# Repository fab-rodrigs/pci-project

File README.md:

# pci-project

[Documento Relatório](https://docs.google.com/document/d/15hXtcBPBoGtcoUK8AWU8GS6HNx2_iXNRZ9IdS8J2mAE/edit?usp=sharing)

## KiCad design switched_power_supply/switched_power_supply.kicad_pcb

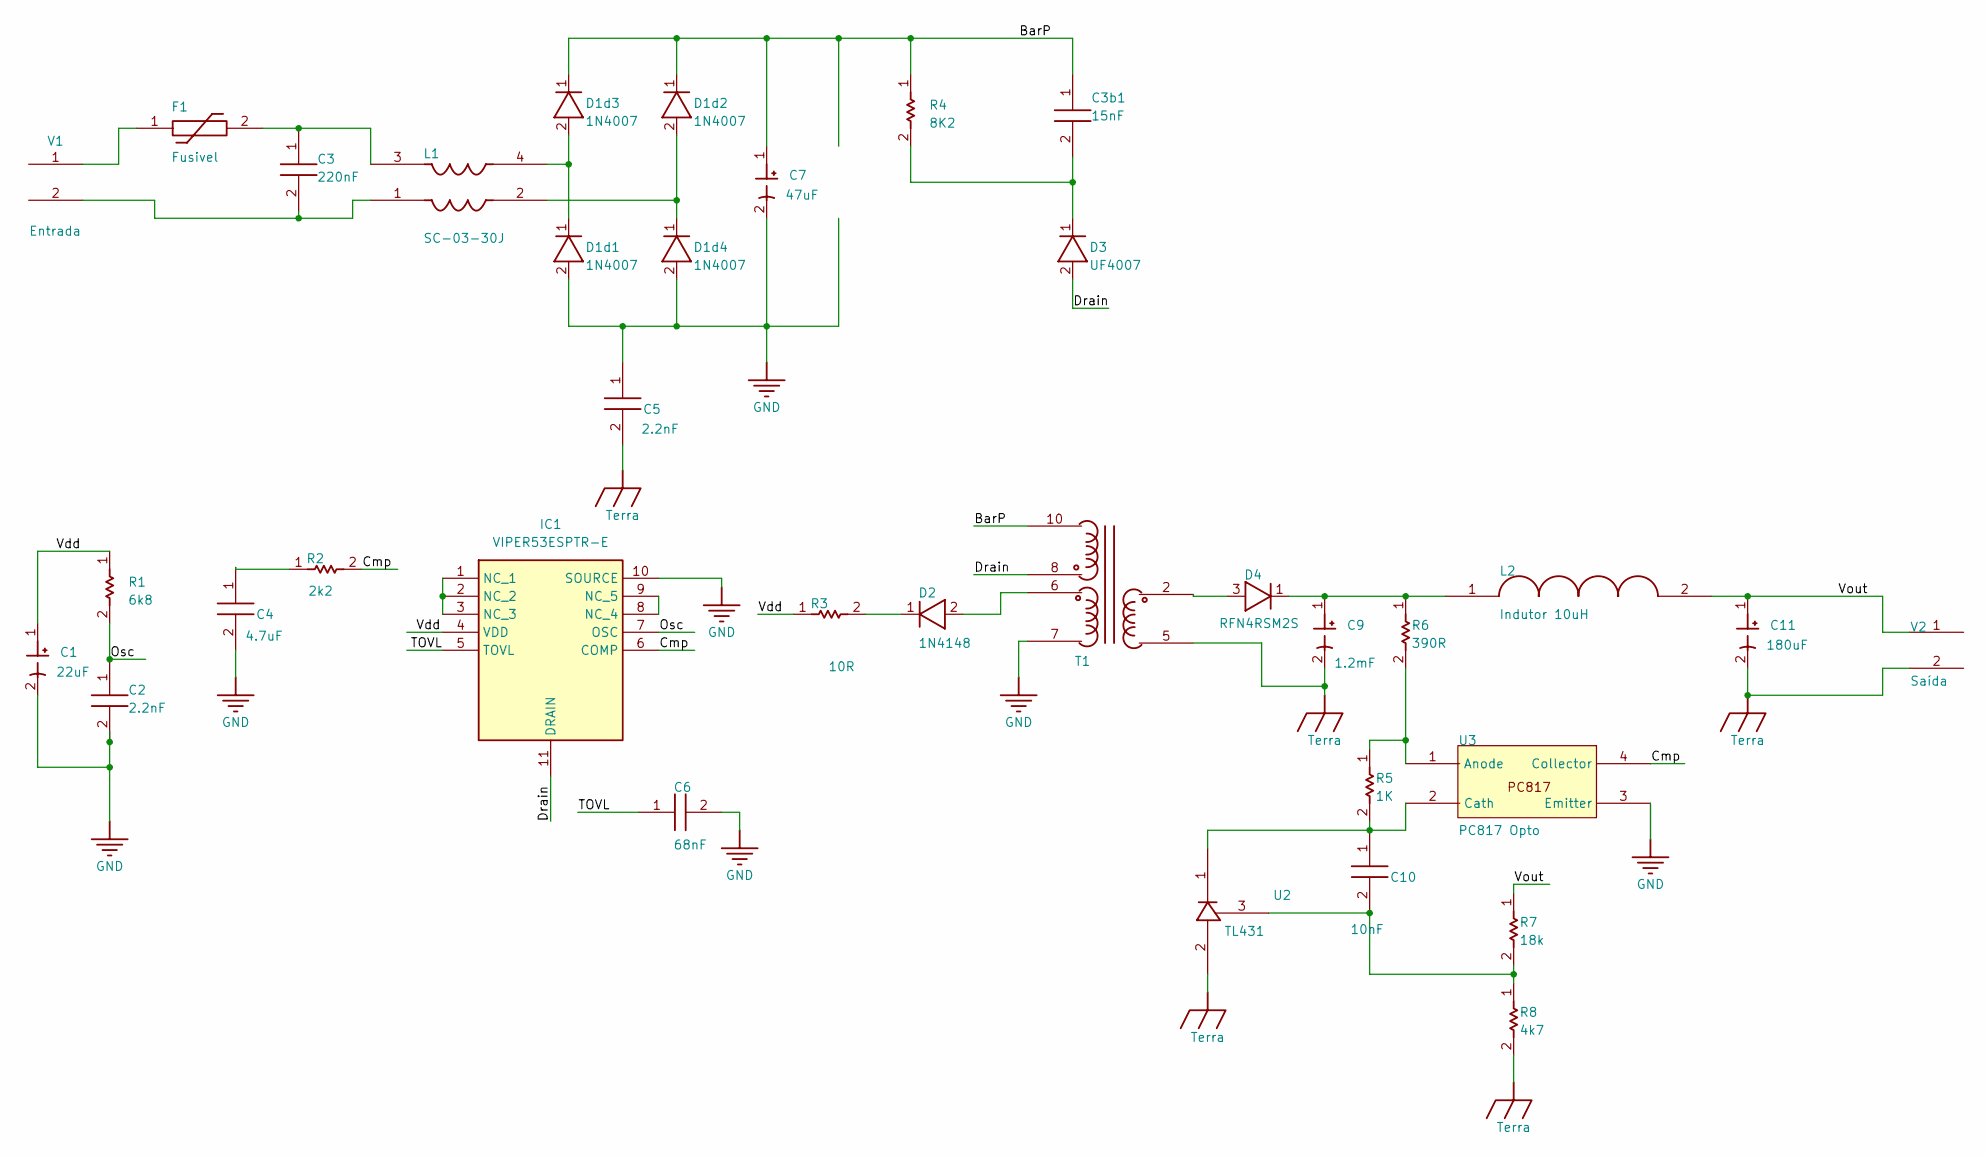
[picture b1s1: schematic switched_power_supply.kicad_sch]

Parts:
C1: Capacitor_Eletrolitico; EEHZT1E331UP
C2: Capacitor Ceramico; CAPC1608X97N
C3: Capacitor_Filme; C_Rect_L18.0mm_W5.0mm_P15.00mm_FKS3_FKP3
C3b1: Capacitor_Filme; C_Rect_L18.0mm_W6.0mm_P15.00mm_FKS3_FKP3; VOLTAGE 15nF
C4: Capacitor Ceramico; CAPC3225X94N
C5: Capacitor_Filme; C_Rect_L7.0mm_W2.5mm_P5.00mm
C6: Capacitor_Filme; CAPC3216X170N
C7: Capacitor_Eletrolitico; CP_Radial_D16.0mm_P7.50mm
C9: Capacitor_Eletrolitico; EEEFK0J332AV
C10: Capacitor_Filme; C1206
C11: Capacitor_Eletrolitico; 16SVPG330M
D1d1, D1d2, D1d3, D1d4: 1N4007; D_A-405_P12.70mm_Horizontal
D2: 1N4148; D_DO-35_SOD27_P7.62mm_Horizontal
D3: UF4007; D_DO-41_SOD81_P7.62mm_Horizontal
D4: RFN4RSM2S; TO-277A
F1: Fusivel; Fuse_Bourns_MF-RG600
IC1: VIPER53ESPTR-E; SOIC127P1410X370-11N; Mouser Part Number 511-VIPER53ESPTR-E
L1: SC-03-30J; L_Axial_L20.0mm_D8.0mm_P25.40mm_Horizontal
L2: Indutor 10uH; INDPM108102X400N
R1, R2, R3, R5: Resistor SMD; R_0805_2012Metric; ML_PART *
R4: Resistor PTH; R_Axial_Power_L25.0mm_W6.4mm_P30.48mm; ML_PART *
R6, R7, R8: Resistor PTH; R_0805_2012Metric; ML_PART *
T1: Transformador_1x2; TRZ 25.010.2
U2: TL431; SOT95P237X112-3N
U3: PC817 Opto; SOIC254P960X420-4N
V1: Entrada; TerminalBlock_bornier-2_P5.08mm
V2: Saída; TerminalBlock_bornier-2_P5.08mm

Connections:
/BarP: C3b1.1, C7.1, D1d2.1 (K), D1d3.1 (K), R4.1, T1.10
/Cmp: IC1.6 (COMP), R2.2, U3.4 (Collector)
/Drain: D3.2 (A), IC1.11 (DRAIN), T1.8
/Osc: C2.1, IC1.7 (OSC), R1.2
/TOVL: C6.1, IC1.5 (TOVL)
/Vdd: C1.1, IC1.4 (VDD), R1.1, R3.1
/Vout: C11.1, L2.2, R7.1, V2.1
GND: C1.2, C2.2, C4.2, C5.1, C6.2, C7.2, D1d1.2 (A), D1d4.2 (A), IC1.10 (SOURCE), T1.7, U3.3 (Emitter)
unnamed: C3.1, F1.2, L1.3
unnamed: C3.2, L1.1, V1.2
unnamed: C4.1, R2.1
unnamed: C10.2, R7.2, R8.1, U2.3
unnamed: D1d1.1 (K), D1d3.2 (A), L1.4
unnamed: D1d2.2 (A), D1d4.1 (K), L1.2
unnamed: D2.2 (A), T1.6
unnamed: D2.1 (K), R3.2
unnamed: C3b1.2, D3.1 (K), R4.2
unnamed: D4.3 (A), T1.2
unnamed: C9.1, D4.1 (K), L2.1, R6.1
unnamed: F1.1, V1.1
unnamed: IC1.1 (NC_1), IC1.2 (NC_2), IC1.3 (NC_3)
unnamed: IC1.8 (NC_4), IC1.9 (NC_5)
unnamed: R5.1, R6.2, U3.1 (Anode)
unnamed: C10.1, R5.2, U2.1, U3.2 (Cath)
Terra: C5.2, C9.2, C11.2, R8.2, T1.5, U2.2, V2.2

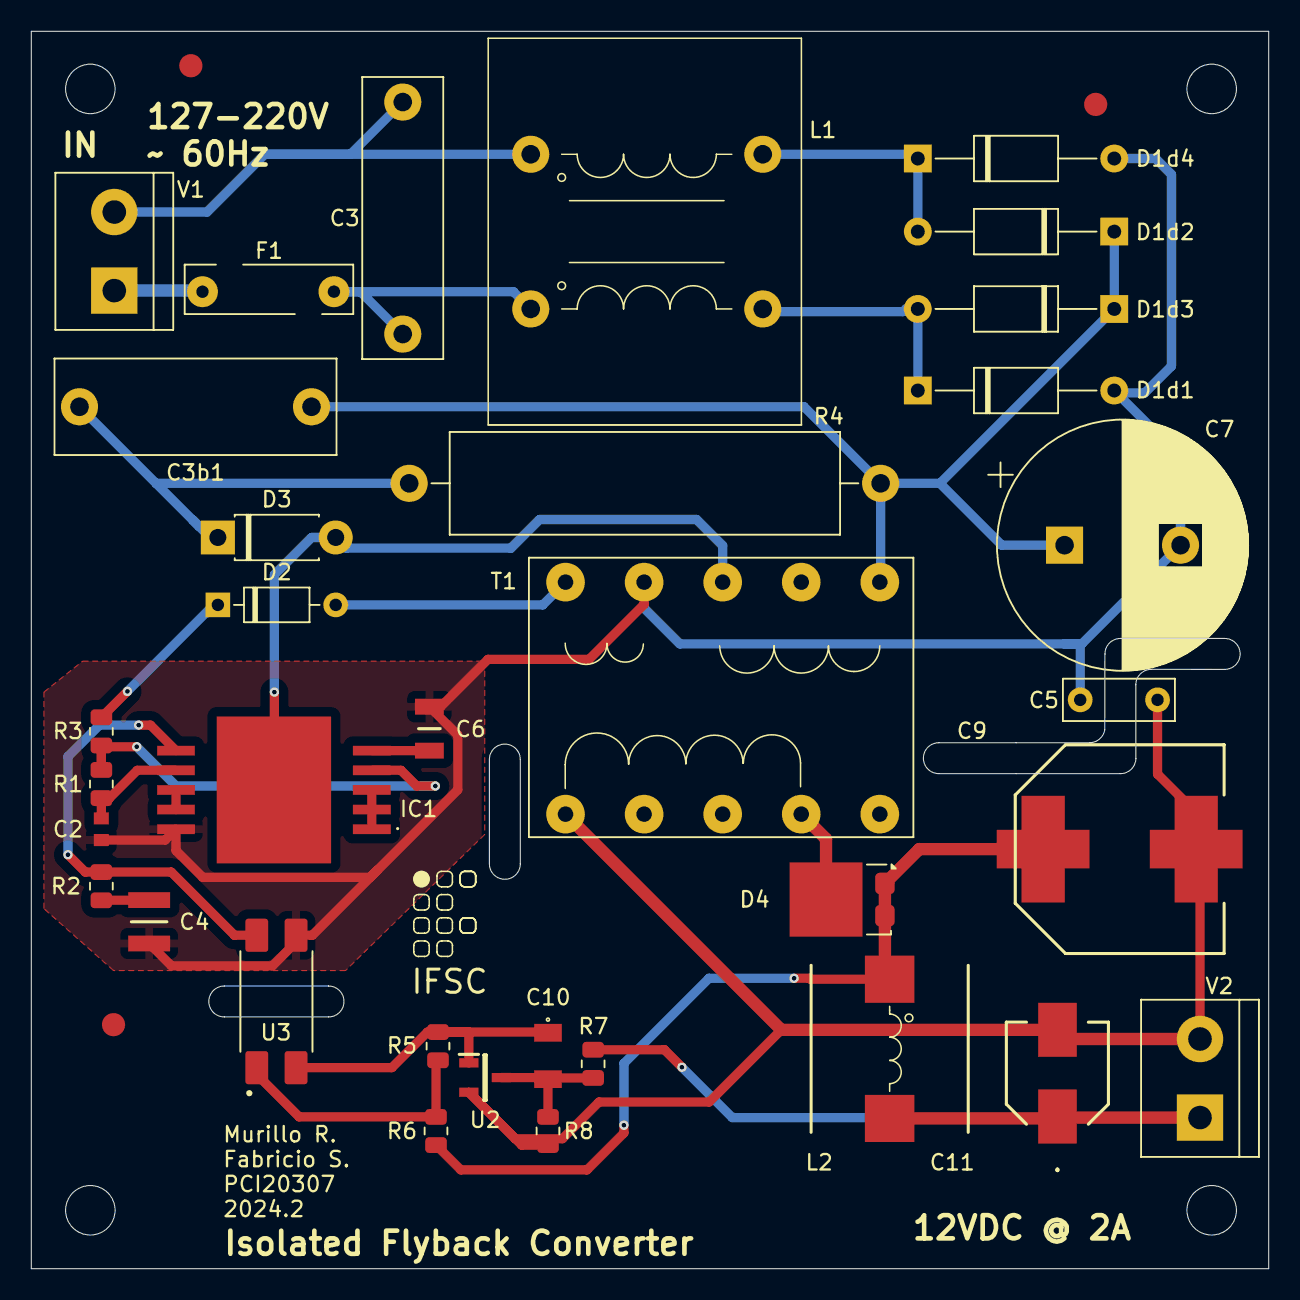
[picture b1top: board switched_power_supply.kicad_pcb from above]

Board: 2 copper layers, 80.0 x 80.0 mm, 34 parts (0 on the bottom side), 25 nets.

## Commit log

2025-02-10 agora vai
2025-02-10 arquivos viper
2025-02-15 teste
2025-02-16 Uploanding files
2025-02-16 Uploading files
2025-02-17 aula 17.02
2025-02-24 footprint EMI ind. corrigido
2025-02-24 pcb atualizado
2025-02-24 quase pronto
2025-03-01 Realizando correções...
2025-03-04 atualização final
